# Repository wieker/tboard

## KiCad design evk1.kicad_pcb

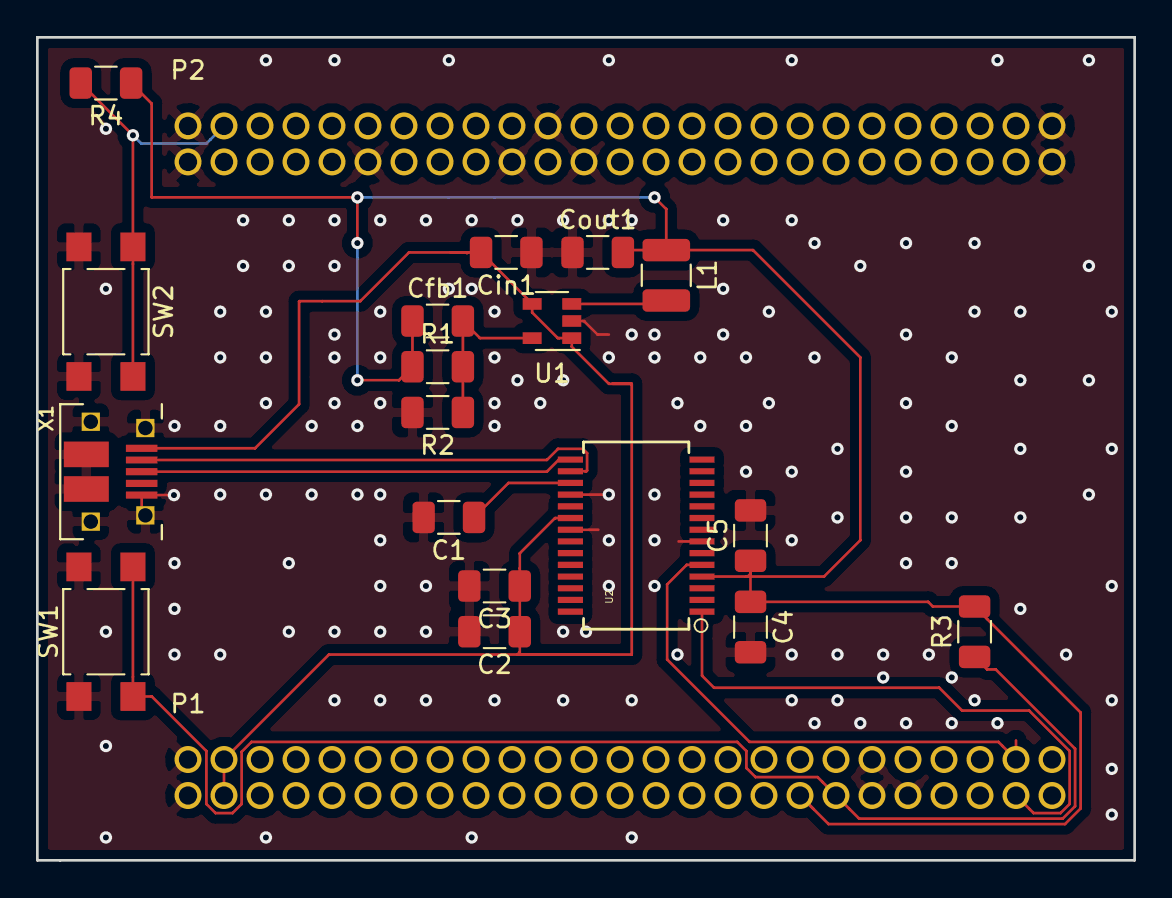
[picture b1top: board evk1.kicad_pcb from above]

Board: 2 copper layers, 61.0 x 45.7 mm, 20 parts (0 on the bottom side), 12 nets.

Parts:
C1: 1uF; C_1206_3216Metric
C2, C4: 4.7uF; C_1206_3216Metric
C3, C5: 0.1uF; C_1206_3216Metric
Cfb1: 22pF; C_1206_3216Metric
Cin1: 2.2uF; C_1206_3216Metric
Cout1: 2.2uF; C_1206_3216Metric
L1: 2.2uH; L_1210_3225Metric
P1, P2: CONN_02X25; Socket_Strip_Straight_2x25
R1: 450kOhm; R_1206_3216Metric
R2, R3, R4: 100kOhm; R_1206_3216Metric
SW1, SW2: SW_Push; SW_SPST_TL3305C
U1: LTC3406B-1.2; SOT-23-5
U2: CY7C65213; SSOP28DB
X1: USBFCI_10103594; FCI_10103594_MILL

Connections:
+3V3: C4.1, C5.1, Cfb1.1, Cout1.2, L1.1, P1.35, R1.1, R3.2, R4.1, U2.4
+5V: C2.1, C3.1, Cin1.2, P1.3, P1.4, U1.1, U1.4, U2.20, X1.VBUS
GND: C1.2, C2.2, C3.2, C4.2, C5.2, Cin1.1, Cout1.1, P1.1, P1.2, P1.39, P1.40, P1.41, P2.1, P2.2, P2.11, P2.19, P2.22, P2.23, P2.49, P2.50, R2.2, SW1.1, SW2.2, U1.2, U2.7, U2.18, U2.21, X1.BASE@1, X1.BASE@2, X1.GND, X1.SPRT@1, X1.SPRT@2, X1.SPRT@3, X1.SPRT@4
unnamed: C1.1, U2.17
unnamed: Cfb1.2, R1.2, R2.1, U1.5
unnamed: L1.2, U1.3
unnamed: P1.37, R3.1, SW1.2
unnamed: P2.4, R4.2, SW2.1
unnamed: U2.15, X1.D+
unnamed: U2.16, X1.D-
NvtRX: P1.47, U2.1
NvtTX: P1.48, U2.5

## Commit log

2019-03-24 initial
